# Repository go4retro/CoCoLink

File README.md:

# CoCoLink - A TANDY Color Computer RS-232 Pak Work-alike with High Speed mods and Sockmaster mods
This cartridge reproduces the functionality of the TANDY Color Computer RS-232 Pak with some performance enchancements.

## Enhancements
* Up to 4 cards are supported in a system ($ff68,$ff6c,$ff7x,$ff7c)
* Supports additional, faster bps rates, including 57,600 bps, 115,200 bps, and 230,400 bps
* Includes support for some of Sockmaster's [mods](http://users.axess.com/twilight/sock/rs232.html "mods"), including:
  * Swappable DCD and DSR lines
  * Auto-RTS (incomplete support at present)

## License
Copyright (C) 2018  RETRO Innovations

These files are free designs; you can redistribute them and/or modify
them under the terms of the Creative Commons Attribution-ShareAlike 
4.0 International License.

You should have received a copy of the license along with this
work. If not, see <http://creativecommons.org/licenses/by-sa/4.0/>.

These files are distributed in the hope that they will be useful,
but WITHOUT ANY WARRANTY; without even the implied warranty of
MERCHANTABILITY or FITNESS FOR A PARTICULAR PURPOSE.  See the
license for more details.

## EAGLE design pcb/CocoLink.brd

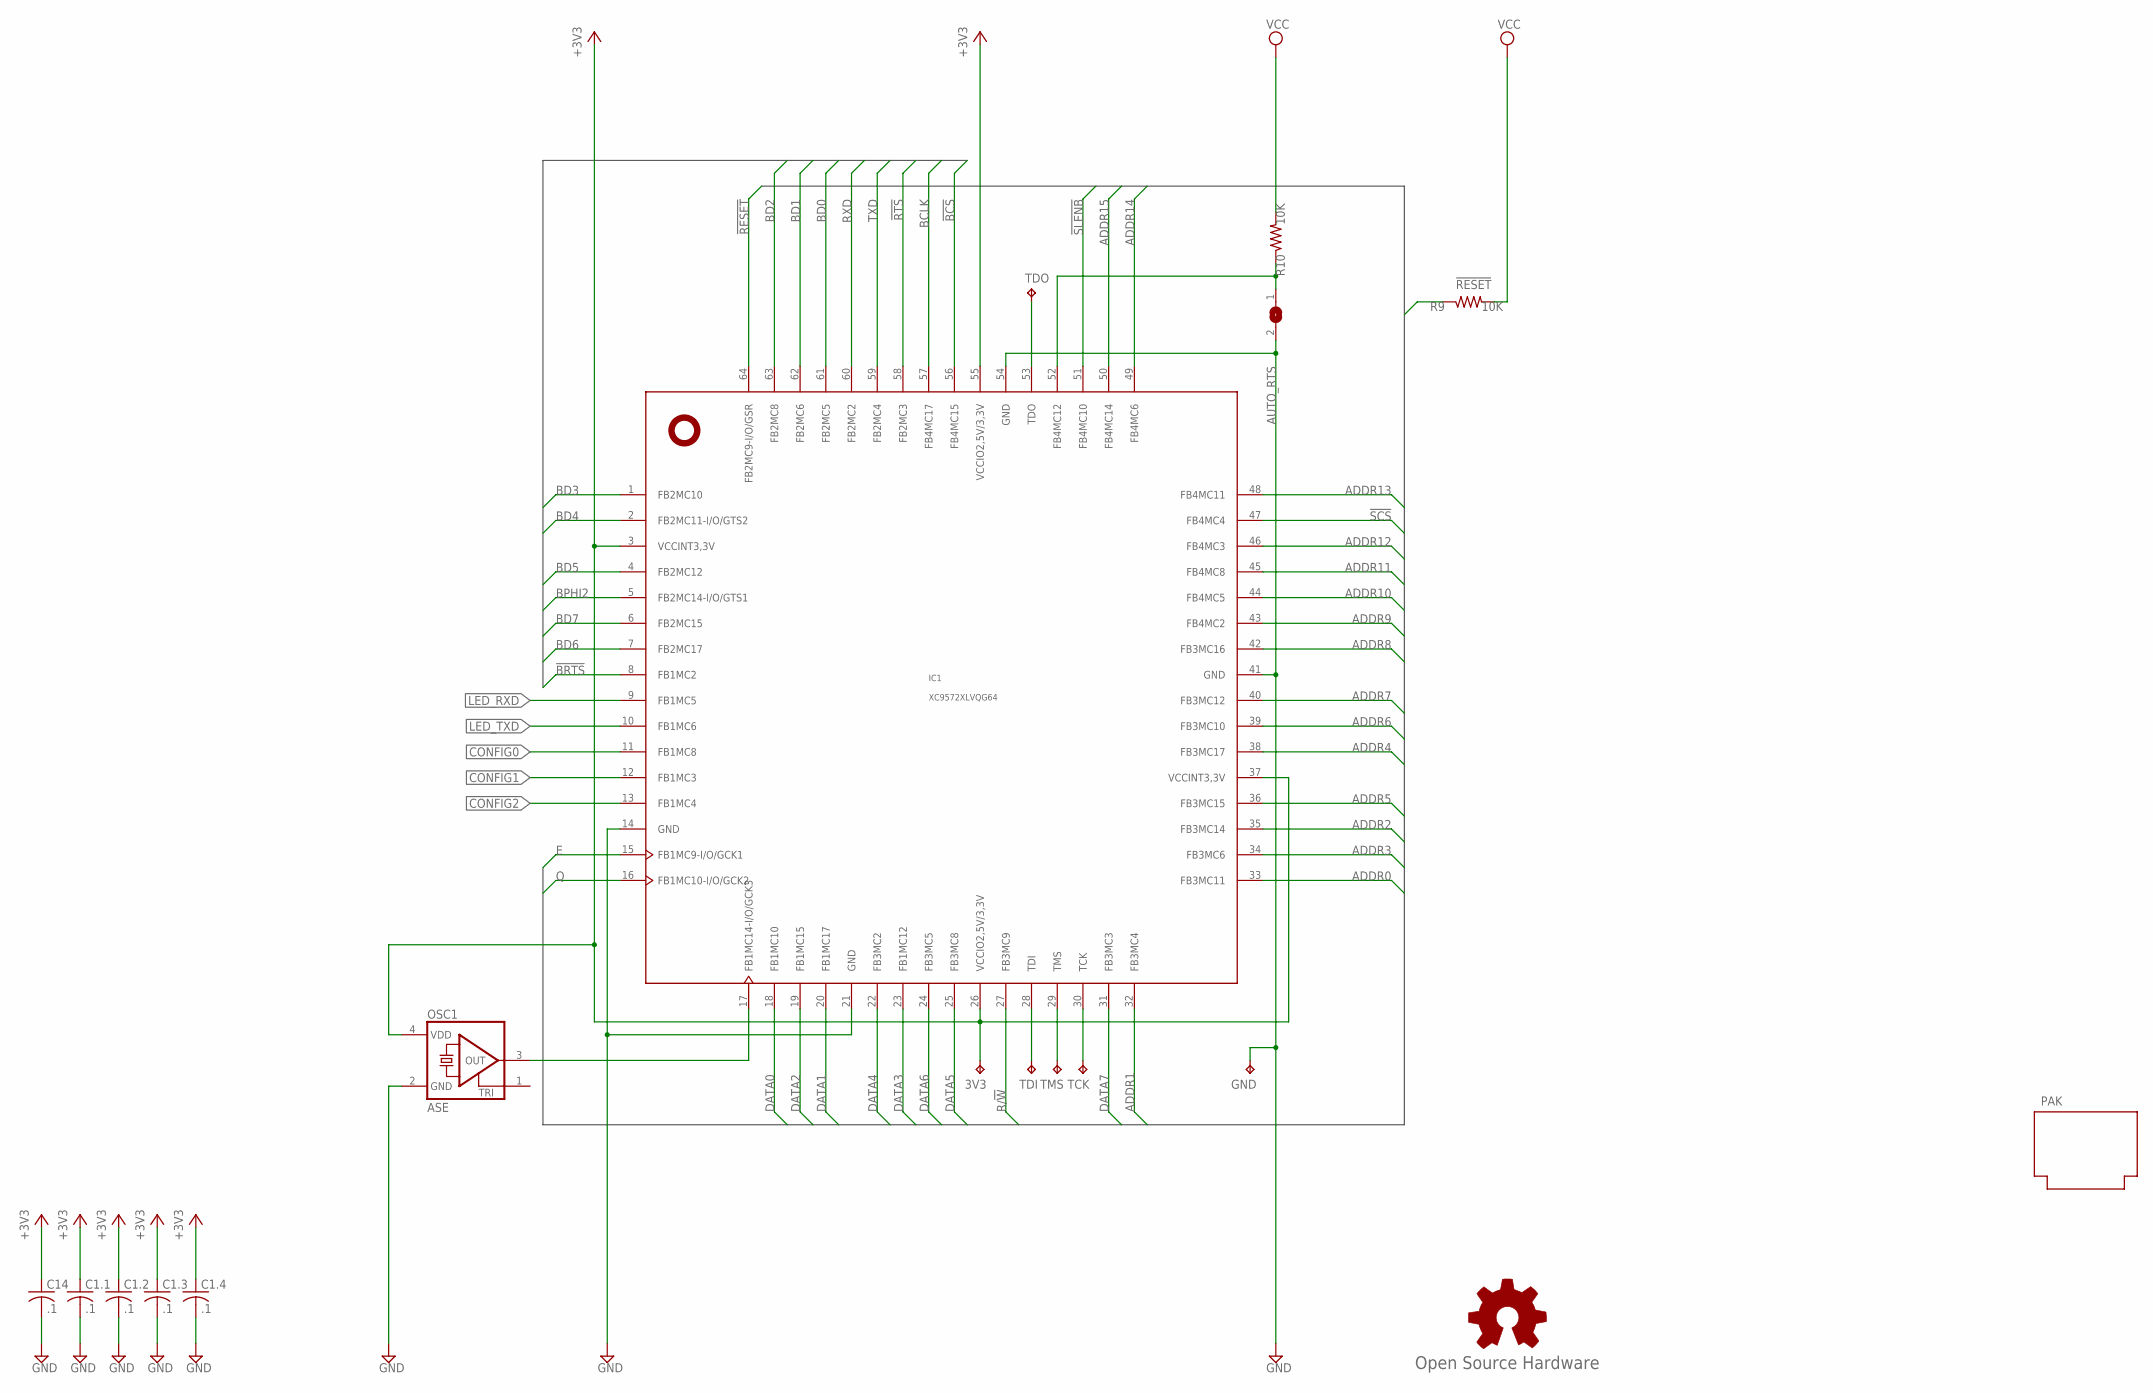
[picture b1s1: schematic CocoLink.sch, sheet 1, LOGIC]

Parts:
3V3: TPTP10R; TP10R
AUTO_RTS: SJ
C1.1, C1.2, C1.3, C1.4, C14: .1; C0402
GND: TPTP10R; TP10R
GOLD_ORB_SM1: Open Source Hardware; OSHW_8MM
IC1: XC9572XLVQG64; VQFP64
OSC1: ASE
PAK: PROGRAM_PAK
R9, R10: 10K; R0402
TCK: TPTP10R; TP10R
TDI: TPTP10R; TP10R
TDO: TPTP10R; TP10R
TMS: TPTP10R; TP10R

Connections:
!BCS: IC1.56 (FB4MC15); also elsewhere on the board
!BRTS: IC1.8 (FB1MC2); also elsewhere on the board
!RESET: IC1.64 (FB2MC9-I/O/GSR), R9.1; also elsewhere on the board
!RTS: IC1.58 (FB2MC3); also elsewhere on the board
!SCS: IC1.47 (FB4MC4); also elsewhere on the board
!SLENB: IC1.51 (FB4MC10); also elsewhere on the board
+3V3: 3V3.TP, C1.1.1, C1.2.1, C1.3.1, C1.4.1, C14.1, IC1.3 (VCCINT3,3V), IC1.26 (VCCIO2,5V/3,3V), IC1.37 (VCCINT3,3V), IC1.55 (VCCIO2,5V/3,3V), OSC1.4 (VDD); also elsewhere on the board
ADDR0: IC1.33 (FB3MC11); also elsewhere on the board
ADDR1: IC1.32 (FB3MC4); also elsewhere on the board
ADDR2: IC1.35 (FB3MC14); also elsewhere on the board
ADDR3: IC1.34 (FB3MC6); also elsewhere on the board
ADDR4: IC1.38 (FB3MC17); also elsewhere on the board
ADDR5: IC1.36 (FB3MC15); also elsewhere on the board
ADDR6: IC1.39 (FB3MC10); also elsewhere on the board
ADDR7: IC1.40 (FB3MC12); also elsewhere on the board
ADDR8: IC1.42 (FB3MC16); also elsewhere on the board
ADDR9: IC1.43 (FB4MC2); also elsewhere on the board
ADDR10: IC1.44 (FB4MC5); also elsewhere on the board
ADDR11: IC1.45 (FB4MC8); also elsewhere on the board
ADDR12: IC1.46 (FB4MC3); also elsewhere on the board
ADDR13: IC1.48 (FB4MC11); also elsewhere on the board
ADDR14: IC1.49 (FB4MC6); also elsewhere on the board
ADDR15: IC1.50 (FB4MC14); also elsewhere on the board
BCLK: IC1.57 (FB4MC17); also elsewhere on the board
BD0: IC1.61 (FB2MC5); also elsewhere on the board
BD1: IC1.62 (FB2MC6); also elsewhere on the board
BD2: IC1.63 (FB2MC8); also elsewhere on the board
BD3: IC1.1 (FB2MC10); also elsewhere on the board
BD4: IC1.2 (FB2MC11-I/O/GTS2); also elsewhere on the board
BD5: IC1.4 (FB2MC12); also elsewhere on the board
BD6: IC1.7 (FB2MC17); also elsewhere on the board
BD7: IC1.6 (FB2MC15); also elsewhere on the board
BPHI2: IC1.5 (FB2MC14-I/O/GTS1); also elsewhere on the board
CONFIG0: IC1.11 (FB1MC8); also elsewhere on the board
CONFIG1: IC1.12 (FB1MC3); also elsewhere on the board
CONFIG2: IC1.13 (FB1MC4); also elsewhere on the board
DATA0: IC1.18 (FB1MC10); also elsewhere on the board
DATA1: IC1.20 (FB1MC17); also elsewhere on the board
DATA2: IC1.19 (FB1MC15); also elsewhere on the board
DATA3: IC1.23 (FB1MC12); also elsewhere on the board
DATA4: IC1.22 (FB3MC2); also elsewhere on the board
DATA5: IC1.25 (FB3MC8); also elsewhere on the board
DATA6: IC1.24 (FB3MC5); also elsewhere on the board
DATA7: IC1.31 (FB3MC3); also elsewhere on the board
E: IC1.15 (FB1MC9-I/O/GCK1); also elsewhere on the board
GND: AUTO_RTS.2, C1.1.2, C1.2.2, C1.3.2, C1.4.2, C14.2, GND.TP, IC1.14 (GND), IC1.21 (GND), IC1.41 (GND), IC1.54 (GND), OSC1.2 (GND); also elsewhere on the board
LED_RXD: IC1.9 (FB1MC5); also elsewhere on the board
LED_TXD: IC1.10 (FB1MC6); also elsewhere on the board
unnamed: IC1.53 (TDO), TDO.TP
unnamed: IC1.28 (TDI), TDI.TP
unnamed: IC1.29 (TMS), TMS.TP
unnamed: IC1.30 (TCK), TCK.TP
unnamed: IC1.17 (FB1MC14-I/O/GCK3), OSC1.3 (OUT)
unnamed: AUTO_RTS.1, IC1.52 (FB4MC12), R10.1
Q: IC1.16 (FB1MC10-I/O/GCK2); also elsewhere on the board
R/!W: IC1.27 (FB3MC9); also elsewhere on the board
RXD: IC1.60 (FB2MC2); also elsewhere on the board
TXD: IC1.59 (FB2MC4); also elsewhere on the board
VCC: R9.2, R10.2; also elsewhere on the board

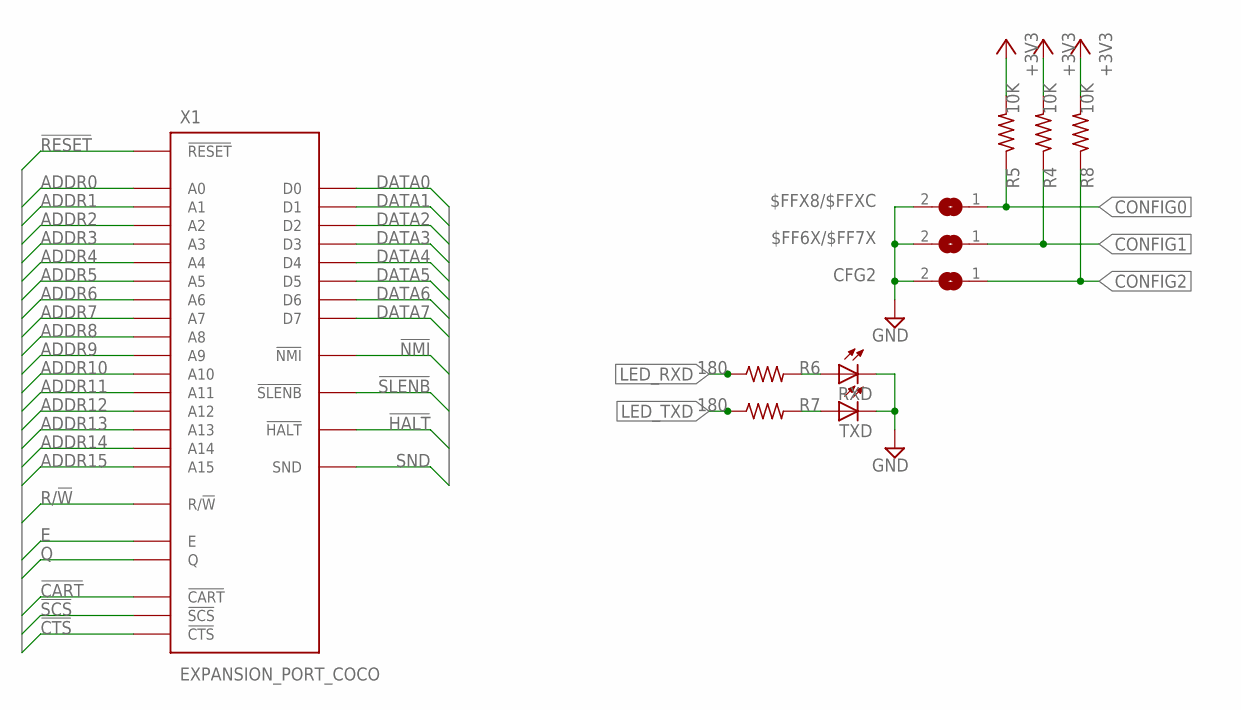
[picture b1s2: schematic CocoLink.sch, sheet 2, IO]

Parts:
$FF6X/$FF7X: SJ
$FFX8/$FFXC: SJ
CFG2: SJ
R4, R5, R8: 10K; R0402
R6, R7: 180; R0402
RXD: LED3MM
TXD: LED3MM
X1: EXPANSION_PORT_COCO; MA20-2

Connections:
!CART: X1.8 (!CART); also elsewhere on the board
!CTS: X1.32 (!CTS)
!HALT: X1.3 (!HALT)
!NMI: X1.4 (!NMI)
!RESET: X1.5 (!RESET); also elsewhere on the board
!SCS: X1.36 (!SCS); also elsewhere on the board
!SLENB: X1.40 (!SLENB); also elsewhere on the board
+3V3: R4.2, R5.2, R8.2; also elsewhere on the board
+12V: X1.2 (+12V)
-12V: X1.1 (-12V)
ADDR0: X1.19 (A0); also elsewhere on the board
ADDR1: X1.20 (A1); also elsewhere on the board
ADDR2: X1.21 (A2); also elsewhere on the board
ADDR3: X1.22 (A3); also elsewhere on the board
ADDR4: X1.23 (A4); also elsewhere on the board
ADDR5: X1.24 (A5); also elsewhere on the board
ADDR6: X1.25 (A6); also elsewhere on the board
ADDR7: X1.26 (A7); also elsewhere on the board
ADDR8: X1.27 (A8); also elsewhere on the board
ADDR9: X1.28 (A9); also elsewhere on the board
ADDR10: X1.29 (A10); also elsewhere on the board
ADDR11: X1.30 (A11); also elsewhere on the board
ADDR12: X1.31 (A12); also elsewhere on the board
ADDR13: X1.37 (A13); also elsewhere on the board
ADDR14: X1.38 (A14); also elsewhere on the board
ADDR15: X1.39 (A15); also elsewhere on the board
CONFIG0: $FFX8/$FFXC.1, R5.1; also elsewhere on the board
CONFIG1: $FF6X/$FF7X.1, R4.1; also elsewhere on the board
CONFIG2: CFG2.1, R8.1; also elsewhere on the board
DATA0: X1.10 (D0); also elsewhere on the board
DATA1: X1.11 (D1); also elsewhere on the board
DATA2: X1.12 (D2); also elsewhere on the board
DATA3: X1.13 (D3); also elsewhere on the board
DATA4: X1.14 (D4); also elsewhere on the board
DATA5: X1.15 (D5); also elsewhere on the board
DATA6: X1.16 (D6); also elsewhere on the board
DATA7: X1.17 (D7); also elsewhere on the board
E: X1.6 (E); also elsewhere on the board
GND: $FF6X/$FF7X.2, $FFX8/$FFXC.2, CFG2.2, RXD.K (C), TXD.K (C), X1.33 (GND), X1.34 (GND); also elsewhere on the board
LED_RXD: R6.1; also elsewhere on the board
LED_TXD: R7.1; also elsewhere on the board
unnamed: R7.2, TXD.A
unnamed: R6.2, RXD.A
Q: X1.7 (Q); also elsewhere on the board
R/!W: X1.18 (R/!W); also elsewhere on the board
SND: X1.35 (SND)
VCC: X1.9 (VCC); also elsewhere on the board

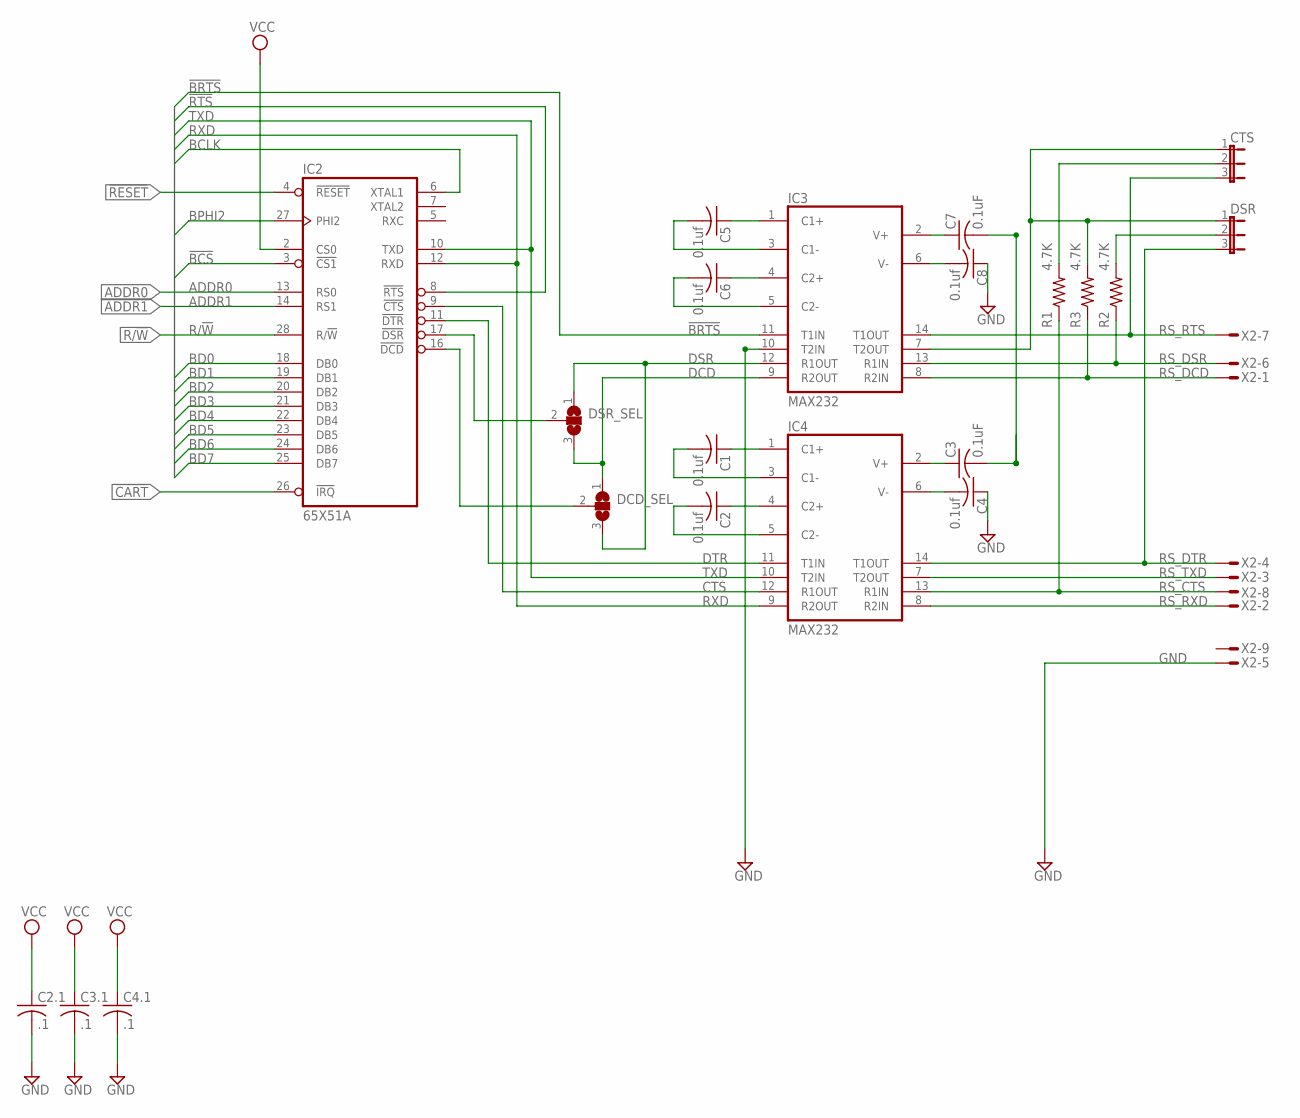
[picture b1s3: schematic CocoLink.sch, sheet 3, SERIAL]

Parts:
C1, C2, C4, C5, C6, C8: 0.1uf; C0402
C2.1, C3.1, C4.1: .1; C0402
C3, C7: 0.1uF; C0402
CTS: JP2E; JP2
DCD_SEL: SJ2W; SJ_2
DSR: JP2E; JP2
DSR_SEL: SJ2W; SJ_2
IC2: 65X51A; DIL28-ROUNDPAD
IC3, IC4: MAX232; SO16
R1, R2, R3: 4.7K; R1206
X2: M09DS; M09D

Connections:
!BCS: IC2.3 (!CS1); also elsewhere on the board
!BRTS: IC3.11 (T1IN); also elsewhere on the board
!CART: IC2.26 (!IRQ); also elsewhere on the board
!RESET: IC2.4 (!RESET); also elsewhere on the board
!RTS: IC2.8 (!RTS); also elsewhere on the board
ACIA_DCD: DCD_SEL.2, IC2.16 (!DCD)
ACIA_DSR: DSR_SEL.2, IC2.17 (!DSR)
ADDR0: IC2.13 (RS0); also elsewhere on the board
ADDR1: IC2.14 (RS1); also elsewhere on the board
BCLK: IC2.6 (XTAL1); also elsewhere on the board
BD0: IC2.18 (DB0); also elsewhere on the board
BD1: IC2.19 (DB1); also elsewhere on the board
BD2: IC2.20 (DB2); also elsewhere on the board
BD3: IC2.21 (DB3); also elsewhere on the board
BD4: IC2.22 (DB4); also elsewhere on the board
BD5: IC2.23 (DB5); also elsewhere on the board
BD6: IC2.24 (DB6); also elsewhere on the board
BD7: IC2.25 (DB7); also elsewhere on the board
BPHI2: IC2.27 (PHI2); also elsewhere on the board
CTS: IC2.9 (!CTS), IC4.12 (R1OUT)
DCD: DCD_SEL.1, DSR_SEL.3, IC3.9 (R2OUT)
DSR: DCD_SEL.3, DSR_SEL.1, IC3.12 (R1OUT)
DTR: IC2.11 (!DTR), IC4.11 (T1IN)
GND: C2.1.2, C3.1.2, C4.1, C4.1.2, C8.1, IC2.1 (GND), IC3.10 (T2IN), IC3.15 (GND), IC4.15 (GND), X2.5; also elsewhere on the board
unnamed: DSR.2, R2.2
unnamed: CTS.1, DSR.1, IC3.7 (T2OUT), R3.2
unnamed: CTS.2, R1.2
unnamed: C1.1, IC4.1 (C1+)
unnamed: C1.2, IC4.3 (C1-)
unnamed: C2.1, IC4.4 (C2+)
unnamed: C2.2, IC4.5 (C2-)
unnamed: C3.1, IC4.2 (V+)
unnamed: C4.2, IC4.6 (V-)
unnamed: C5.1, IC3.1 (C1+)
unnamed: C5.2, IC3.3 (C1-)
unnamed: C6.1, IC3.4 (C2+)
unnamed: C6.2, IC3.5 (C2-)
unnamed: C7.1, IC3.2 (V+)
unnamed: C8.2, IC3.6 (V-)
R/!W: IC2.28 (R/!W); also elsewhere on the board
RS_CTS: IC4.13 (R1IN), R1.1, X2.8
RS_DCD: IC3.13 (R1IN), R2.1, X2.6
RS_DSR: IC3.8 (R2IN), R3.1, X2.1
RS_DTR: DSR.3, IC4.14 (T1OUT), X2.4
RS_RTS: CTS.3, IC3.14 (T1OUT), X2.7
RS_RXD: IC4.8 (R2IN), X2.2
RS_TXD: IC4.7 (T2OUT), X2.3
RXD: IC2.12 (RXD), IC4.9 (R2OUT); also elsewhere on the board
TXD: IC2.10 (TXD), IC4.10 (T2IN); also elsewhere on the board
VCC: C2.1.1, C3.2, C3.1.1, C4.1.1, C7.2, IC2.2 (CS0), IC2.15 (VCC), IC3.16 (VCC), IC4.16 (VCC); also elsewhere on the board

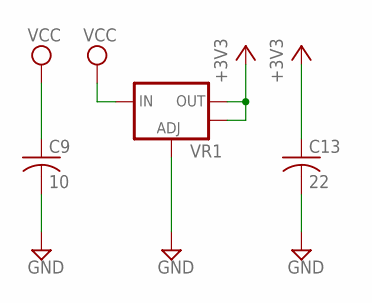
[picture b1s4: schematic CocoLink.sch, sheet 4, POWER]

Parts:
C9: 10; C0805
C13: 22; C0805
VR1: V_REG_LM1117SOT223; SOT223

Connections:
+3V3: C13.1, VR1.2 (OUT), VR1.4 (OUT); also elsewhere on the board
GND: C9.2, C13.2, VR1.1 (ADJ); also elsewhere on the board
VCC: C9.1, VR1.3 (IN); also elsewhere on the board

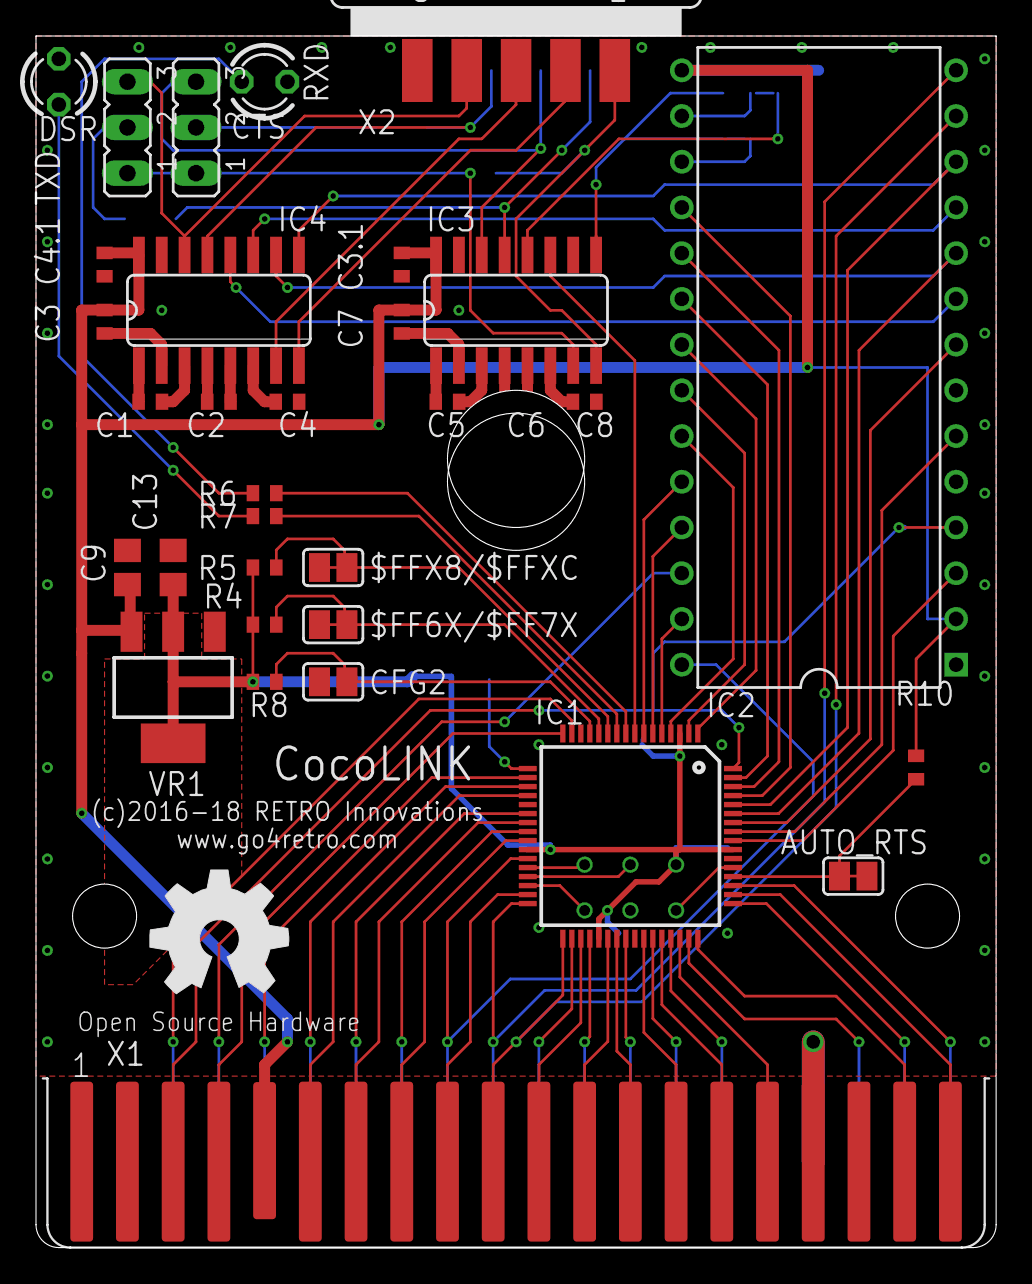
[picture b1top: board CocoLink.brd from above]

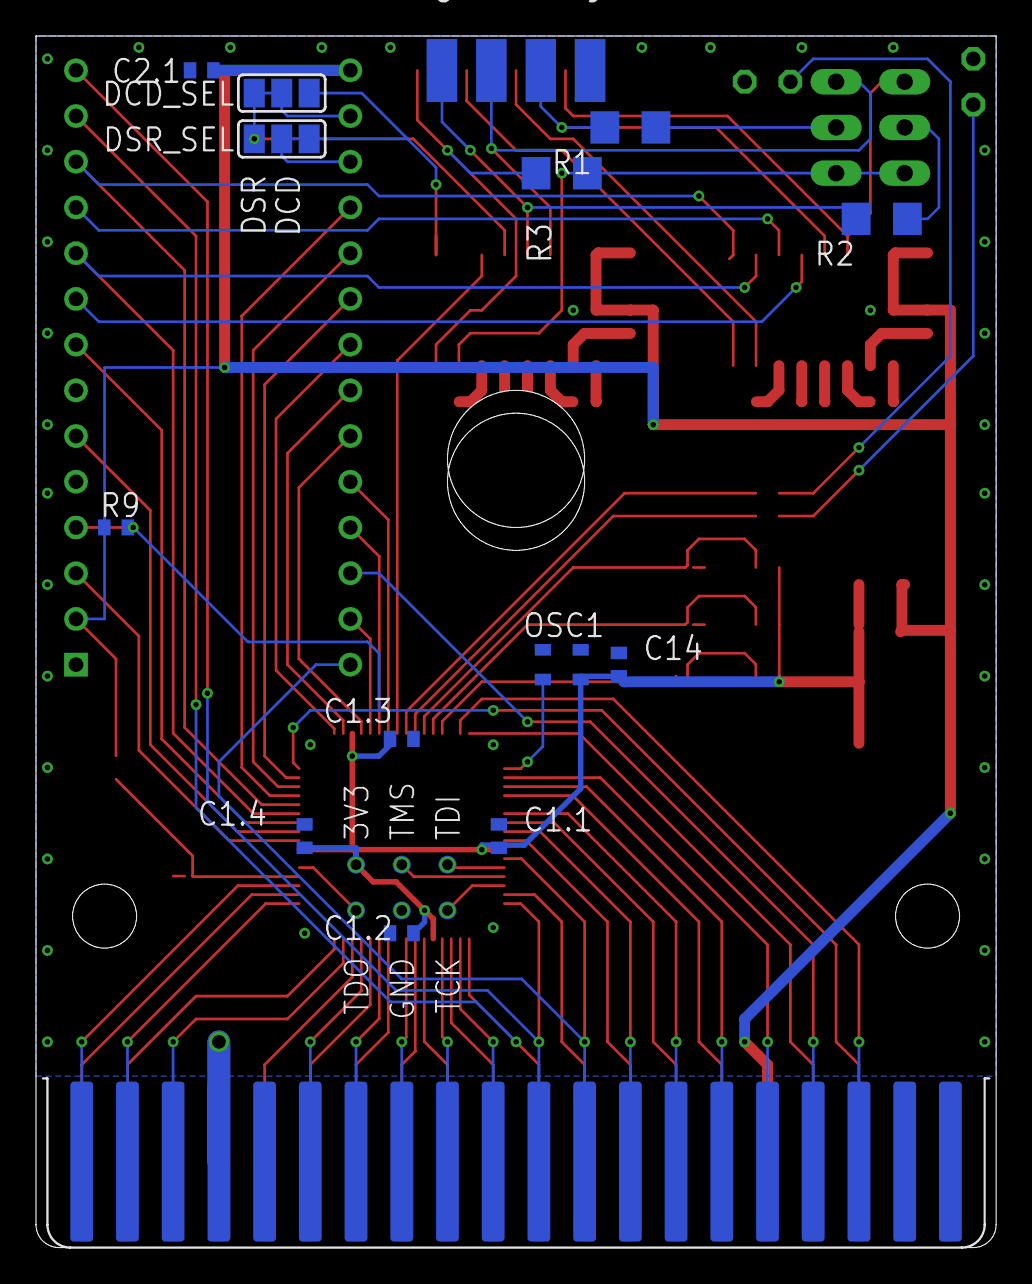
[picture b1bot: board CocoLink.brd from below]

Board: 2 copper layers, 53.3 x 67.3 mm, 54 parts (19 on the bottom side), 90 nets.

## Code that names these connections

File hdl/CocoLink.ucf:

#PACE: Start of Constraints generated by PACE

#PACE: Start of PACE I/O Pin Assignments
NET "_acia_ce"  LOC = "P56"  ; 
NET "_reset"  LOC = "P64"  ; 
NET "_slenb"  LOC = "P51"  ; 
NET "acia_clock_in"  LOC = "P17"  ; 
NET "acia_clock_out"  LOC = "P57"  ; 
NET "acia_data<0>"  LOC = "P61"  ; 
NET "acia_data<1>"  LOC = "P62"  ; 
NET "acia_data<2>"  LOC = "P63"  ; 
NET "acia_data<3>"  LOC = "P1"  ; 
NET "acia_data<4>"  LOC = "P2"  ; 
NET "acia_data<5>"  LOC = "P4"  ; 
NET "acia_data<6>"  LOC = "P7"  ; 
NET "acia_data<7>"  LOC = "P6"  ; 
NET "acia_phi2"  LOC = "P5"  ; 
NET "acia_rts"  LOC = "P58"  ;
NET "acia_rxd"  LOC = "P60"  ; 
NET "acia_txd"  LOC = "P59"  ; 
NET "address<0>"  LOC = "P33"  ; 
NET "address<10>"  LOC = "P44"  ; 
NET "address<11>"  LOC = "P45"  ; 
NET "address<12>"  LOC = "P46"  ; 
NET "address<13>"  LOC = "P48"  ; 
NET "address<14>"  LOC = "P49"  ; 
NET "address<15>"  LOC = "P50"  ; 
NET "address<1>"  LOC = "P32"  ; 
NET "address<2>"  LOC = "P35"  ; 
NET "address<3>"  LOC = "P34"  ; 
NET "address<4>"  LOC = "P38"  ; 
NET "address<5>"  LOC = "P36"  ; 
NET "address<6>"  LOC = "P39"  ; 
NET "address<7>"  LOC = "P40"  ; 
NET "address<8>"  LOC = "P42"  ; 
NET "address<9>"  LOC = "P43"  ; 
NET "cfg<0>"  LOC = "P11"  ; 
NET "cfg<1>"  LOC = "P12"  ; 
NET "data<0>"  LOC = "P18"  ; 
NET "data<1>"  LOC = "P20"  ; 
NET "data<2>"  LOC = "P19"  ; 
NET "data<3>"  LOC = "P23"  ; 
NET "data<4>"  LOC = "P22"  ; 
NET "data<5>"  LOC = "P25"  ; 
NET "data<6>"  LOC = "P24"  ; 
NET "data<7>"  LOC = "P31"  ; 
NET "e"  LOC = "P15"  ; 
NET "led_rxd"  LOC = "P9"  ; 
NET "led_txd"  LOC = "P10"  ; 
NET "r_w"  LOC = "P27"  ; 
NET "rs_rts"  LOC = "P8"  ;

#PACE: Start of PACE Area Constraints

#PACE: Start of PACE Prohibit Constraints

#PACE: End of Constraints generated by PACE

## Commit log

2019-01-21 Added some text on enhancements
2019-01-21 Fixed Markdown link

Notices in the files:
pcb/CocoLink.brd:
(c)2016-18 RETRO Innovations
parts and their libraries:
SparkFun: Licensing: CC v3.0 Share-Alike You are welcome to use this library for commercial purposes.
